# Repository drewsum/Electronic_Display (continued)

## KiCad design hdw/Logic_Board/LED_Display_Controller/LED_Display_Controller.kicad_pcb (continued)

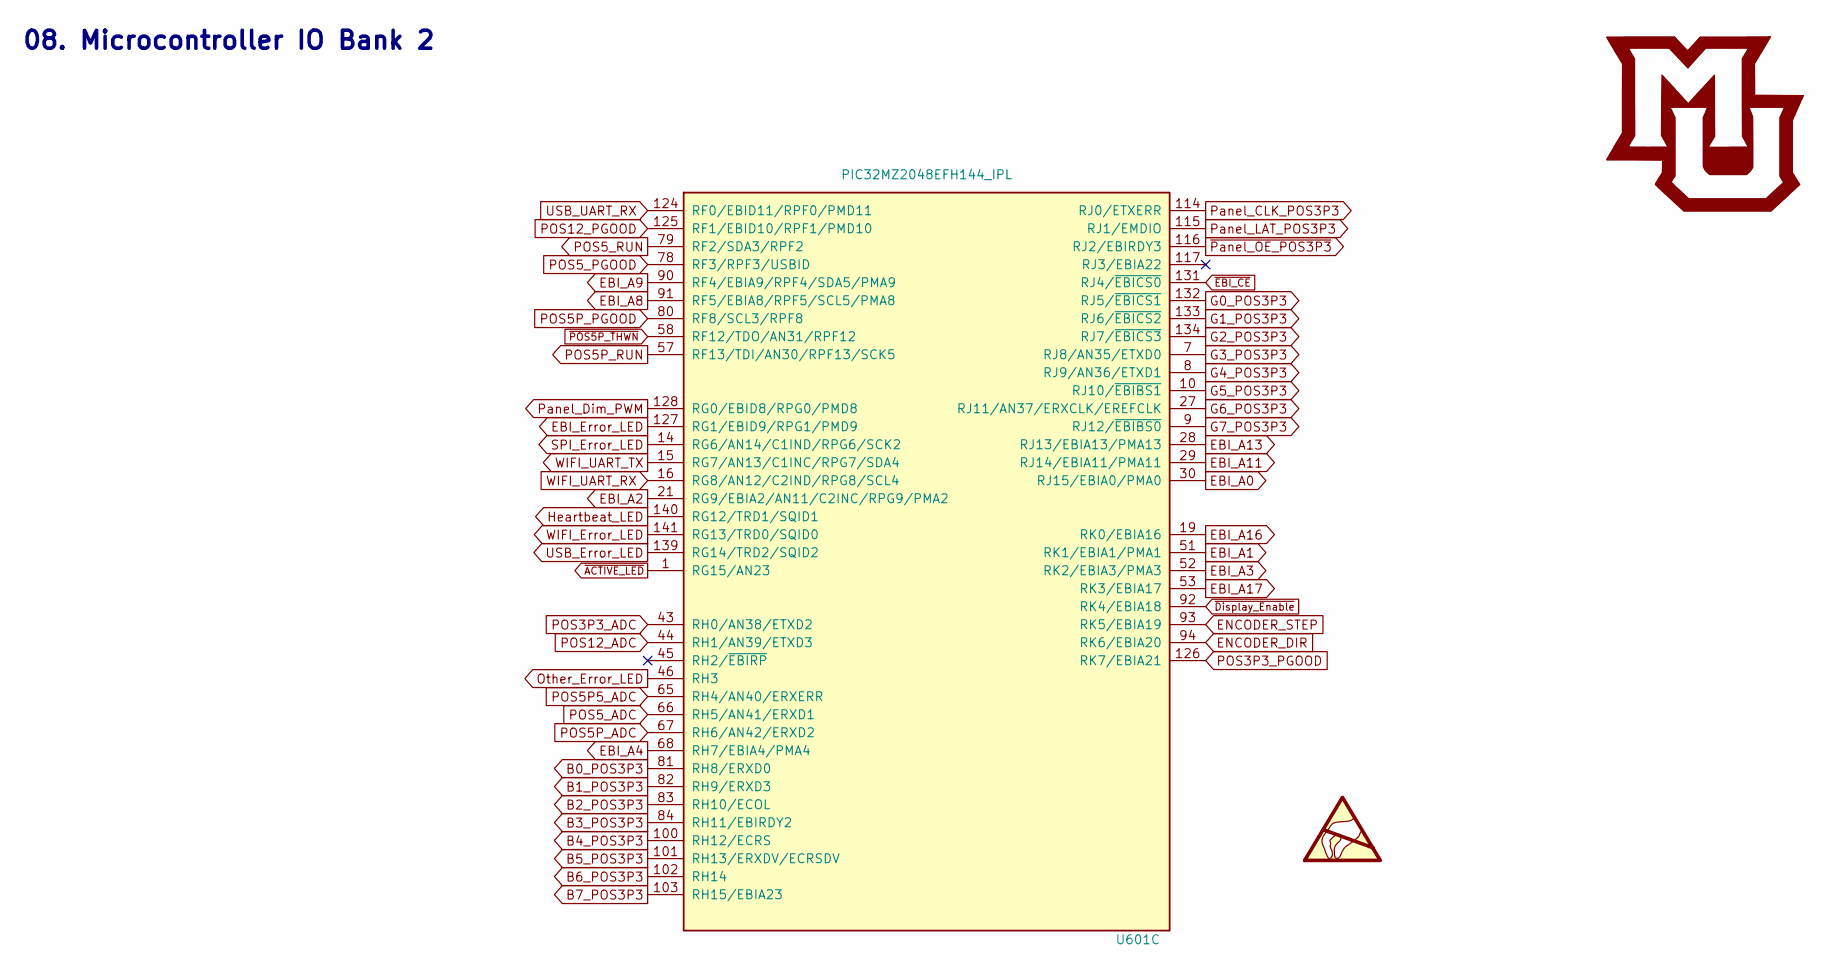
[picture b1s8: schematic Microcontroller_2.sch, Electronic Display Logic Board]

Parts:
U601: PIC32MZ2048EFH144_IPL; TQFP-144_20x20mm_Pitch0.5mm; Digi-Key PN PIC32MZ2048EFH144-I/PL-ND

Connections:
B0_POS3P3: U601.81 (RH8/ERXD0); also elsewhere on the board
B1_POS3P3: U601.82 (RH9/ERXD3); also elsewhere on the board
B2_POS3P3: U601.83 (RH10/ECOL); also elsewhere on the board
B3_POS3P3: U601.84 (RH11/EBIRDY2); also elsewhere on the board
B4_POS3P3: U601.100 (RH12/ECRS); also elsewhere on the board
B5_POS3P3: U601.101 (RH13/ERXDV/ECRSDV); also elsewhere on the board
B6_POS3P3: U601.102 (RH14); also elsewhere on the board
B7_POS3P3: U601.103 (RH15/EBIA23); also elsewhere on the board
EBI_A0: U601.30 (RJ15/EBIA0/PMA0); also elsewhere on the board
EBI_A1: U601.51 (RK1/EBIA1/PMA1); also elsewhere on the board
EBI_A2: U601.21 (RG9/EBIA2/AN11/C2INC/RPG9/PMA2); also elsewhere on the board
EBI_A3: U601.52 (RK2/EBIA3/PMA3); also elsewhere on the board
EBI_A4: U601.68 (RH7/EBIA4/PMA4); also elsewhere on the board
EBI_A8: U601.91 (RF5/EBIA8/RPF5/SCL5/PMA8); also elsewhere on the board
EBI_A9: U601.90 (RF4/EBIA9/RPF4/SDA5/PMA9); also elsewhere on the board
EBI_A11: U601.29 (RJ14/EBIA11/PMA11); also elsewhere on the board
EBI_A13: U601.28 (RJ13/EBIA13/PMA13); also elsewhere on the board
EBI_A16: U601.19 (RK0/EBIA16); also elsewhere on the board
EBI_A17: U601.53 (RK3/EBIA17); also elsewhere on the board
EBI_Error_LED: U601.127 (RG1/EBID9/RPG1/PMD9); also elsewhere on the board
ENCODER_DIR: U601.94 (RK6/EBIA20); also elsewhere on the board
ENCODER_STEP: U601.93 (RK5/EBIA19); also elsewhere on the board
G0_POS3P3: U601.132 (RJ5/~EBICS1~); also elsewhere on the board
G1_POS3P3: U601.133 (RJ6/~EBICS2~); also elsewhere on the board
G2_POS3P3: U601.134 (RJ7/~EBICS3~); also elsewhere on the board
G3_POS3P3: U601.7 (RJ8/AN35/ETXD0); also elsewhere on the board
G4_POS3P3: U601.8 (RJ9/AN36/ETXD1); also elsewhere on the board
G5_POS3P3: U601.10 (RJ10/~EBIBS1~); also elsewhere on the board
G6_POS3P3: U601.27 (RJ11/AN37/ERXCLK/EREFCLK); also elsewhere on the board
G7_POS3P3: U601.9 (RJ12/~EBIBS0~); also elsewhere on the board
Heartbeat_LED: U601.140 (RG12/TRD1/SQID1); also elsewhere on the board
Other_Error_LED: U601.46 (RH3); also elsewhere on the board
POS3P3_ADC: U601.43 (RH0/AN38/ETXD2); also elsewhere on the board
POS3P3_PGOOD: U601.126 (RK7/EBIA21); also elsewhere on the board
POS5P5_ADC: U601.65 (RH4/AN40/ERXERR); also elsewhere on the board
POS5P_ADC: U601.67 (RH6/AN42/ERXD2); also elsewhere on the board
POS5P_PGOOD: U601.80 (RF8/SCL3/RPF8); also elsewhere on the board
POS5P_RUN: U601.57 (RF13/TDI/AN30/RPF13/SCK5); also elsewhere on the board
POS5_ADC: U601.66 (RH5/AN41/ERXD1); also elsewhere on the board
POS5_PGOOD: U601.78 (RF3/RPF3/USBID); also elsewhere on the board
POS5_RUN: U601.79 (RF2/SDA3/RPF2); also elsewhere on the board
POS12_ADC: U601.44 (RH1/AN39/ETXD3); also elsewhere on the board
POS12_PGOOD: U601.125 (RF1/EBID10/RPF1/PMD10); also elsewhere on the board
Panel_CLK_POS3P3: U601.114 (RJ0/ETXERR); also elsewhere on the board
Panel_Dim_PWM: U601.128 (RG0/EBID8/RPG0/PMD8); also elsewhere on the board
Panel_LAT_POS3P3: U601.115 (RJ1/EMDIO); also elsewhere on the board
SPI_Error_LED: U601.14 (RG6/AN14/C1IND/RPG6/SCK2); also elsewhere on the board
USB_Error_LED: U601.139 (RG14/TRD2/SQID2); also elsewhere on the board
USB_UART_RX: U601.124 (RF0/EBID11/RPF0/PMD11); also elsewhere on the board
WIFI_Error_LED: U601.141 (RG13/TRD0/SQID0); also elsewhere on the board
WIFI_UART_RX: U601.16 (RG8/AN12/C2IND/RPG8/SCL4); also elsewhere on the board
WIFI_UART_TX: U601.15 (RG7/AN13/C1INC/RPG7/SDA4); also elsewhere on the board
~ACTIVE_LED: U601.1 (RG15/AN23); also elsewhere on the board
~Display_Enable: U601.92 (RK4/EBIA18); also elsewhere on the board
~EBI_CE: U601.131 (RJ4/~EBICS0~); also elsewhere on the board
~POS5P_THWN: U601.58 (RF12/TDO/AN31/RPF12); also elsewhere on the board
~Panel_OE_POS3P3: U601.116 (RJ2/EBIRDY3); also elsewhere on the board

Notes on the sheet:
08. Microcontroller IO Bank 2

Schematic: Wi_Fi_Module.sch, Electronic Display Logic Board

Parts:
C901: 100uF; CP_Tantalum_Case-B_EIA-3528-21_Reflow; Voltage 6.3V; Tolerance 20%; Digi-Key PN 478-3130-1-ND
C902, C905, C906, C907: 0.1uF; C_0603; Voltage 50V; Digi-Key PN 311-1344-1-ND
C903: 10nF; C_0603; Voltage 50V; Digi-Key PN 1276-1921-1-ND
C904: 1nF; C_0603; Voltage 50V; Digi-Key PN 1276-1018-1-ND
D901: PESD3V3L4UG; SOT-353_SC-70-5; Digi-Key PN 1727-3827-1-ND
D902: Green; LED_0603; Digi-Key PN 160-1446-1-ND
Q901: BSS214NW; SOT-323_SC-70; Digi-Key PN BSS214NWH6327XTSA1CT-ND
R901, R906, R909: 100; R_0603; Tolerance 1%; Digi-Key PN A106047CT-ND
R902, R903, R904, R905, R907, R910, R911: 10k; R_0603; Tolerance 1%; Digi-Key PN RMCF0603FT10K0CT-ND
R908: 10; R_0603; Tolerance 1%; Digi-Key PN YAG3351CT-ND
R912: 0; R_0603; Tolerance 1%; Digi-Key PN 311-0.0GRCT-ND
R913: 1k; R_0603; Tolerance 1%; Digi-Key PN RMCF0603FT1K00CT-ND
U901: ESP8266 Socket; ESP8266_Socket
U902: 74LVC1G00; SOT-353_SC-70-5; Digi-Key PN 296-9846-1-ND
U903: 74LVC1G86; SOT-353_SC-70-5; Digi-Key PN 296-9854-1-ND

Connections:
+3V3: C901.1, C902.1, C903.1, C904.1, C906.1, C907.1, R902.1, R903.1, R905.1, R907.1, R911.1, R913.1, U901.8, U902.5 (VCC), U903.5 (VCC); also elsewhere on the board
GND: C901.2, C902.2, C903.2, C904.2, C905.2, C906.2, C907.2, D901.2 (A), Q901.2 (S), R904.2, R910.2, R912.2, U901.1, U902.3 (GND), U903.3 (GND); also elsewhere on the board
unnamed: C905.1, D901.5 (K4), R905.2, R906.2, U901.6
unnamed: D901.3 (K2), R903.2, R909.2, U901.2
unnamed: D901.4 (K3), R901.2, R902.2, U901.7
unnamed: D902.1 (K), U903.4
unnamed: D902.2 (A), R913.2
unnamed: Q901.1 (G), R907.2, R908.2
unnamed: Q901.3 (D), R906.1
unnamed: R910.1, U902.4, U903.1
unnamed: R911.2, R912.1, U903.2
WIFI_CHPD: D901.1 (K1), R904.1, U901.4; also elsewhere on the board
WIFI_UART_RX: R909.1, U902.1; also elsewhere on the board
WIFI_UART_TX: R901.1, U902.2; also elsewhere on the board
~WIFI_RESET: R908.1; also elsewhere on the board

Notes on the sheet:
09. WiFi Module

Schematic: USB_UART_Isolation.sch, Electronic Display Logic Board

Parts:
C1001, C1003: 0.1uF; C_0603; Voltage 50V; Digi-Key PN 311-1344-1-ND
C1002: 0.56uF; C_2220; Voltage 250VAC; Digi-Key PN 565-4707-1-ND
R1001, R1002, R1007, R1008: 100; R_0603; Tolerance 1%; Digi-Key PN A106047CT-ND
R1003, R1004, R1005, R1006: 10k; R_0603; Tolerance 1%; Digi-Key PN RMCF0603FT10K0CT-ND
U1001: ISO7321C; SOIC-8_3.9x4.9mm_Pitch1.27mm; Digi-Key PN 296-42102-1-ND

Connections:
+3V3: C1001.1, R1003.1, R1004.1, U1001.1 (VCC1); also elsewhere on the board
+5V_USB: C1003.1, R1005.1, R1006.1, U1001.8 (VCC2); also elsewhere on the board
GND: C1001.2, C1002.1, U1001.4 (GND1); also elsewhere on the board
GND_USB: C1002.2, C1003.2, U1001.5 (GND2); also elsewhere on the board
unnamed: R1001.2, R1003.2, U1001.2 (OUTA)
unnamed: R1002.2, R1004.2, U1001.3 (INB)
unnamed: R1005.2, R1008.2, U1001.6 (OUTB)
unnamed: R1006.2, R1007.2, U1001.7 (INA)
USB_UART_RX: R1001.1; also elsewhere on the board
USB_UART_RX_ISO: R1007.1; also elsewhere on the board
USB_UART_TX: R1002.1; also elsewhere on the board
USB_UART_TX_ISO: R1008.1; also elsewhere on the board

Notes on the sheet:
10. USB UART Digital Isolation

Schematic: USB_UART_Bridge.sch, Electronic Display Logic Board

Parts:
C1101, C1102, C1103, C1104, C1105, C1107, C1108, C1111: 0.1uF; C_0603; Voltage 50V; Digi-Key PN 311-1344-1-ND
C1106: 4.7uF; C_0805; Voltage 10V; Digi-Key PN 1276-2972-1-ND
C1109, C1110: 47pF; C_0603; Voltage 50V; Digi-Key PN 478-1171-1-ND
D1101: Green; LED_0603; Digi-Key PN 160-1446-1-ND
D1102: Yellow; LED_0603; Digi-Key PN 160-1448-1-ND
DOC1101: COM_Port_Settings
J1101: USB_B_Mini; USB_Mini-B; Digi-Key PN 732-2109-1-ND
L1101, L1102: 600R 0.5A; L_0603; Digi-Key PN 732-2389-1-ND
R1101, R1105: 10k; R_0603; Tolerance 1%; Digi-Key PN RMCF0603FT10K0CT-ND
R1102: 487k; R_0603; Tolerance 1%; Digi-Key PN 311-487KHRCT-ND
R1103: 6.04k; R_0603; Tolerance 1%; Digi-Key PN RMCF0603FT6K04CT-ND
R1104: 40.2k; R_0603; Tolerance 1%; Digi-Key PN 311-40.2KHRCT-ND
R1106, R1109: 1k; R_0603; Tolerance 1%; Digi-Key PN RMCF0603FT1K00CT-ND
R1107, R1108: 27; R_0603; Tolerance 1%; Digi-Key PN RMCF0603FT27R0CT-ND
U1101: LT6700-1-S6; TSOT-23-6; Digi-Key PN LT6700CS6-1#TRMPBFCT-ND
U1102: FT234XD; DFN-12-1EP_3x3mm_Pitch0.45mm; Digi-Key PN 768-1178-1-ND
U1103: 74LVC1G06; SOT-353_SC-70-5; Digi-Key PN 296-8484-1-ND
U1104: TPD3S014DBVR; SOT-23-6; Digi-Key PN 296-38835-1-ND

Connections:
+5V_USB: C1102.1, C1103.1, C1104.1, C1105.1, C1106.1, C1108.1, R1101.1, R1102.1, R1105.1, R1106.1, R1109.1, U1101.5 (Vs), U1102.4 (VCC), U1102.9 (VCCIO), U1103.5 (VCC), U1104.4 (OUT); also elsewhere on the board
/USB UART Bridge/BRIDGE_USB+: R1107.2, U1102.12 (USBDP)
/USB UART Bridge/BRIDGE_USB-: R1108.2, U1102.1 (USBDM)
/USB UART Bridge/CONN_USB+: C1109.1, J1101.3 (D+), R1107.1, U1104.6 (D1)
/USB UART Bridge/CONN_USB-: C1110.1, J1101.2 (D-), R1108.1, U1104.5 (D2)
/USB UART Bridge/POS5_USB_PGOOD: R1105.2, U1101.1 (OUTA), U1101.6 (OUTB), U1103.2
GND_USB: C1101.2, C1102.2, C1103.2, C1104.2, C1105.2, C1106.2, C1107.2, C1108.2, C1109.2, C1110.2, C1111.2, J1101.5 (GND), L1102.1, R1104.2, U1101.2 (GND), U1102.5 (GND), U1102.13 (GND), U1103.3 (GND), U1104.2 (GND); also elsewhere on the board
unnamed: C1101.1, R1101.2, U1102.2 (~RESET)
unnamed: C1107.1, U1102.3 (3V3OUT)
unnamed: C1111.1, L1101.2, U1104.1 (EN), U1104.3 (IN)
unnamed: D1101.1 (K), U1103.4
unnamed: D1101.2 (A), R1106.2
unnamed: D1102.2 (A), R1109.2
unnamed: J1101.1 (VBUS), L1101.1
unnamed: J1101.6 (Shield), L1102.2
unnamed: R1102.2, R1103.1, U1101.3 (+INA)
unnamed: R1103.2, R1104.1, U1101.4 (-INB)
USB_UART_RX_ISO: U1102.7 (TXD); also elsewhere on the board
USB_UART_TX_ISO: U1102.10 (RXD); also elsewhere on the board
~USB_ACTIVE: D1102.1 (K), U1102.6 (CBUS0)

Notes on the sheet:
11. USB UART Bridge

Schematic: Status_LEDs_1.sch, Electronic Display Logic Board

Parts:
C1201, C1202, C1203, C1204, C1205, C1206, C1207, C1208, C1209, C1210, C1211, C1212, C1213, C1214: 0.1uF; C_0603; Voltage 50V; Digi-Key PN 311-1344-1-ND
D1201, D1202, D1203, D1204, D1205, D1207: Red; LED_0603; Digi-Key PN 160-1447-1-ND
D1206, D1208, D1209, D1210, D1211, D1212, D1213: Green; LED_0603; Digi-Key PN 160-1446-1-ND
R1201, R1202, R1205, R1206, R1209, R1210, R1213, R1215, R1217, R1219, R1221, R1222, R1227, R1228, R1231: 10k; R_0603; Tolerance 1%; Digi-Key PN RMCF0603FT10K0CT-ND
R1203, R1204, R1207, R1208, R1211, R1212, R1214, R1216, R1218, R1220, R1223, R1229, R1230: 1k; R_0603; Tolerance 1%; Digi-Key PN RMCF0603FT1K00CT-ND
R1224, R1225, R1226: 0; R_0603; Tolerance 1%; Digi-Key PN 311-0.0GRCT-ND
U1201, U1202, U1203, U1204, U1205, U1206, U1207, U1208, U1209, U1210, U1211, U1213, U1214: 74LVC1G06; SOT-353_SC-70-5; Digi-Key PN 296-8484-1-ND
U1212: 4040; TSSOP-16_4.4x5mm_Pitch0.65mm; Digi-Key PN 296-12761-1-ND

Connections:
+3V3: C1201.1, C1202.1, C1203.1, C1204.1, C1205.1, C1206.1, C1207.1, C1208.1, C1209.1, C1210.1, C1211.1, C1212.1, C1213.1, C1214.1, R1201.1, R1203.1, R1204.1, R1207.1, R1208.1, R1211.1, R1212.1, R1214.1, R1216.1, R1218.1, R1220.1, R1223.1, R1229.1, R1230.1, R1231.1, U1201.5 (VCC), U1202.5 (VCC), U1203.5 (VCC), U1204.5 (VCC), U1205.5 (VCC), U1206.5 (VCC), U1207.5 (VCC), U1208.5 (VCC), U1209.5 (VCC), U1210.5 (VCC), U1211.5 (VCC), U1212.16 (VDD), U1213.5 (VCC), U1214.5 (VCC); also elsewhere on the board
EBI_Error_LED: R1206.1, U1204.2; also elsewhere on the board
GND: C1201.2, C1202.2, C1203.2, C1204.2, C1205.2, C1206.2, C1207.2, C1208.2, C1209.2, C1210.2, C1211.2, C1212.2, C1213.2, C1214.2, R1202.2, R1205.2, R1206.2, R1209.2, R1210.2, R1213.2, R1215.2, R1217.2, R1219.2, R1221.2, R1222.2, R1227.2, R1228.2, U1201.3 (GND), U1202.3 (GND), U1203.3 (GND), U1204.3 (GND), U1205.3 (GND), U1206.3 (GND), U1207.3 (GND), U1208.3 (GND), U1209.3 (GND), U1210.3 (GND), U1211.3 (GND), U1212.8 (VSS), U1213.3 (GND), U1214.3 (GND); also elsewhere on the board
Heartbeat_LED: R1210.1, U1206.2; also elsewhere on the board
unnamed: D1201.1 (K), U1201.4
unnamed: D1201.2 (A), R1203.2
unnamed: D1202.1 (K), U1202.4
unnamed: D1202.2 (A), R1204.2
unnamed: D1203.1 (K), U1203.4
unnamed: D1203.2 (A), R1207.2
unnamed: D1204.1 (K), U1204.4
unnamed: D1204.2 (A), R1208.2
unnamed: D1205.1 (K), U1205.4
unnamed: D1205.2 (A), R1211.2
unnamed: D1206.1 (K), U1206.4
unnamed: D1206.2 (A), R1212.2
unnamed: D1207.1 (K), U1207.4
unnamed: D1207.2 (A), R1214.2
unnamed: D1208.1 (K), U1208.4
unnamed: D1208.2 (A), R1216.2
unnamed: D1209.1 (K), U1209.4
unnamed: D1209.2 (A), R1218.2
unnamed: D1210.1 (K), U1210.4
unnamed: D1210.2 (A), R1220.2
unnamed: D1211.1 (K), U1211.4
unnamed: D1211.2 (A), R1223.2
unnamed: D1212.1 (K), U1213.4
unnamed: D1212.2 (A), R1229.2
unnamed: D1213.1 (K), U1214.4
unnamed: D1213.2 (A), R1230.2
unnamed: R1221.1, U1212.11 (Reset)
unnamed: R1224.1, R1225.1, R1226.1, R1228.1, U1214.2
unnamed: R1224.2, U1212.3 (Q4)
unnamed: R1225.2, U1212.4 (Q6)
unnamed: R1226.2, U1212.15 (Q10)
Other_Error_LED: R1213.1, U1207.2; also elsewhere on the board
Panel_LAT_POS3P3: R1231.2, U1212.10 (CLK); also elsewhere on the board
Row_A_POS3P3: R1222.1, U1211.2; also elsewhere on the board
Row_B_POS3P3: R1227.1, U1213.2; also elsewhere on the board
Row_C_POS3P3: R1215.1, U1208.2; also elsewhere on the board
Row_D_POS3P3: R1217.1, U1209.2; also elsewhere on the board
Row_E_POS3P3: R1219.1, U1210.2; also elsewhere on the board
SPI_Error_LED: R1202.1, U1202.2; also elsewhere on the board
USB_Error_LED: R1209.1, U1205.2; also elsewhere on the board
WIFI_Error_LED: R1205.1, U1203.2; also elsewhere on the board
~ACTIVE_LED: R1201.2, U1201.2; also elsewhere on the board

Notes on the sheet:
12. Status LEDs Bank 1

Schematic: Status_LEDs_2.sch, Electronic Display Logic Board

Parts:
C1301, C1302, C1303, C1304: 0.1uF; C_0603; Voltage 50V; Digi-Key PN 311-1344-1-ND
D1301, D1302, D1303, D1304: Green; LED_0603; Digi-Key PN 160-1446-1-ND
R1301, R1302, R1303, R1304: 1k; R_0603; Tolerance 1%; Digi-Key PN RMCF0603FT1K00CT-ND
U1301, U1302, U1303, U1304: 74LVC1G06; SOT-353_SC-70-5; Digi-Key PN 296-8484-1-ND

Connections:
+3V3: C1301.1, C1302.1, C1303.1, C1304.1, R1301.1, R1302.1, R1303.1, R1304.1, U1301.5 (VCC), U1302.5 (VCC), U1303.5 (VCC), U1304.5 (VCC); also elsewhere on the board
GND: C1301.2, C1302.2, C1303.2, C1304.2, U1301.3 (GND), U1302.3 (GND), U1303.3 (GND), U1304.3 (GND); also elsewhere on the board
unnamed: D1301.1 (K), U1301.4
unnamed: D1301.2 (A), R1301.2
unnamed: D1302.1 (K), U1302.4
unnamed: D1302.2 (A), R1302.2
unnamed: D1303.1 (K), U1303.4
unnamed: D1303.2 (A), R1303.2
unnamed: D1304.1 (K), U1304.4
unnamed: D1304.2 (A), R1304.2
POS3P3_PGOOD: U1302.2; also elsewhere on the board
POS5P_PGOOD: U1304.2; also elsewhere on the board
POS5_PGOOD: U1303.2; also elsewhere on the board
POS12_PGOOD: U1301.2; also elsewhere on the board

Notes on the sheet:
13. Status LEDs Bank 2

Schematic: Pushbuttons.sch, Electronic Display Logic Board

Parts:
C1401, C1402, C1403, C1404, C1405: 0.1uF; C_0603; Voltage 50V; Digi-Key PN 311-1344-1-ND
D1401: PESD3V3L4UG; SOT-353_SC-70-5; Digi-Key PN 1727-3827-1-ND
J1401: Encoder Ext; Pin_Header_Straight_1x05_Pitch2.54mm
R1401, R1402, R1405, R1406, R1407, R1408: 10k; R_0603; Tolerance 1%; Digi-Key PN RMCF0603FT10K0CT-ND
R1403, R1404: 1k; R_0603; Tolerance 1%; Digi-Key PN RMCF0603FT1K00CT-ND
SW1401: Display Enable; SW_PUSH_6mm
SW1402: Brightness/Enable; ACZ11BR4E-15FA1-20C; Digi-Key PN 102-1753-ND
U1401: MAX6816; SOT-143; Digi-Key PN MAX6816EUS+TCT-ND
U1402: 74LVC2G14; SOT-363_SC-70-6; Digi-Key PN 296-13011-1-ND
U1403: 74LVC1G79; SOT-353_SC-70-5; Digi-Key PN 296-9850-1-ND

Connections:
+3V3: C1401.1, C1404.1, C1405.1, R1401.1, R1402.1, R1405.1, U1401.4 (Vcc), U1402.5 (VCC), U1403.5 (VCC); also elsewhere on the board
ENCODER_DIR: R1408.1, U1403.4 (Q); also elsewhere on the board
ENCODER_STEP: R1407.1, U1402.6, U1403.1 (D); also elsewhere on the board
GND: C1401.2, C1402.2, C1403.2, C1404.2, C1405.2, D1401.2 (A), J1401.2, J1401.5, R1406.2, R1407.2, R1408.2, SW1401.1, SW1402.C, SW1402.S2, U1401.1 (GND), U1402.2 (GND), U1403.3 (GND); also elsewhere on the board
unnamed: C1402.1, R1404.1, U1402.3
unnamed: C1403.1, R1403.1, U1402.1
unnamed: D1401.1 (K1), J1401.1, R1402.2, R1404.2, SW1402.B
unnamed: D1401.3 (K2), J1401.3, R1401.2, R1403.2, SW1402.A
unnamed: D1401.4 (K3), J1401.4, SW1401.2, SW1402.S1, U1401.2 (In)
unnamed: R1406.1, U1402.4, U1403.2 (C)
~Display_Enable: R1405.2, U1401.3 (Out); also elsewhere on the board

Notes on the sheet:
Turning rotary encoder will adjust display master brightness Pressing encoder switch will toggle display on/off state
14. Pushbuttons

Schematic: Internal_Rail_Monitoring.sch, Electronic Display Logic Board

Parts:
C1501, C1502, C1503, C1504, C1505: 330pF; C_0603; Voltage 50V; Digi-Key PN 399-6880-1-ND
D1501, D1502, D1503, D1504, D1505: BZT52C3V3T; D_SOD-523; Digi-Key PN BZT52C3V3T-TPMSCT-ND
R1501, R1502, R1503, R1504, R1505, R1506, R1507, R1508, R1509: 10k; R_0603; Tolerance 1%; Digi-Key PN RMCF0603FT10K0CT-ND
R1510: 1k; R_0603; Tolerance 1%; Digi-Key PN RMCF0603FT1K00CT-ND

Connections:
+3V3: R1501.1; also elsewhere on the board
+5.5V: R1507.1; also elsewhere on the board
+5V: R1505.1; also elsewhere on the board
+5VP: R1503.1; also elsewhere on the board
+12V: R1509.1; also elsewhere on the board
GND: C1501.2, C1502.2, C1503.2, C1504.2, C1505.2, D1501.2 (A), D1502.2 (A), D1503.2 (A), D1504.2 (A), D1505.2 (A), R1502.2, R1504.2, R1506.2, R1508.2, R1510.2; also elsewhere on the board
POS3P3_ADC: C1501.1, D1501.1 (K), R1501.2, R1502.1; also elsewhere on the board
POS5P5_ADC: C1504.1, D1504.1 (K), R1507.2, R1508.1; also elsewhere on the board
POS5P_ADC: C1502.1, D1502.1 (K), R1503.2, R1504.1; also elsewhere on the board
POS5_ADC: C1503.1, D1503.1 (K), R1505.2, R1506.1; also elsewhere on the board
POS12_ADC: C1505.1, D1505.1 (K), R1509.2, R1510.1; also elsewhere on the board

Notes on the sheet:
15. Internal Rail Monitoring

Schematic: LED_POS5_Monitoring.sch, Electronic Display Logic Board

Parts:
C1601: 10uF; CP_Tantalum_Case-B_EIA-3528-21_Reflow; Voltage 16V; Tolerance 10%; Digi-Key PN 478-8236-1-ND
C1602, C1603, C1604, C1605, C1607, C1608, C1609: 0.1uF; C_0603; Voltage 50V; Digi-Key PN 311-1344-1-ND
C1606: 100uF; CP_Tantalum_Case-B_EIA-3528-21_Reflow; Voltage 6.3V; Tolerance 20%; Digi-Key PN 478-3130-1-ND
J1601: POS5P EXT; Pin_Header_Straight_1x02_Pitch2.54mm
J1602: POS5P PGOOD; Pin_Header_Straight_1x02_Pitch2.54mm
J1603: POS5P_THWN; Pin_Header_Straight_1x02_Pitch2.54mm
J1604: POS5P_RUN; Pin_Header_Straight_1x02_Pitch2.54mm
R1601: 200; R_0603; Tolerance 1%; Digi-Key PN P200HCT-ND
R1602: 680; R_0603; Tolerance 1%; Digi-Key PN P680HCT-ND
R1603, R1604: 1k; R_0603; Tolerance 1%; Digi-Key PN RMCF0603FT1K00CT-ND
R1605, R1606, R1607, R1608, R1609, R1610: 10k; R_0603; Tolerance 1%; Digi-Key PN RMCF0603FT10K0CT-ND
U1601: LM1117-ADJ; SOT-223-3_TabPin2; Digi-Key PN LM1117IMPX-ADJ/NOPBCT-ND
U1602, U1606: NUP2202; SOT-363_SC-70-6; Digi-Key PN NUP2202W1T2GOSCT-ND
U1603, U1604, U1605: 74LVC1G17; SOT-353_SC-70-5; Digi-Key PN 296-11934-1-ND

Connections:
+3V3: C1608.1, C1609.1, U1604.5 (VCC), U1605.5 (VCC); also elsewhere on the board
+5.5V: C1605.1, C1606.1, C1607.1, R1601.1, U1601.2 (VO), U1602.5, U1603.5 (VCC), U1606.5; also elsewhere on the board
+5VP: C1604.1, J1601.1; also elsewhere on the board
+12V: C1601.1, C1602.1, U1601.3 (VI); also elsewhere on the board
GND: C1601.2, C1602.2, C1603.2, C1604.2, C1605.2, C1606.2, C1607.2, C1608.2, C1609.2, J1601.2, J1602.2, J1603.2, J1604.2, R1602.2, R1605.2, R1606.2, R1607.2, R1608.2, R1609.2, R1610.2, U1602.2, U1603.3 (GND), U1604.3 (GND), U1605.3 (GND), U1606.2; also elsewhere on the board
unnamed: C1603.1, R1601.2, R1602.1, U1601.1 (ADJ)
unnamed: J1602.1, R1603.2
unnamed: J1603.1, R1604.2
unnamed: J1604.1, R1608.1, U1603.4, U1606.1
unnamed: R1603.1, R1606.1, U1602.6, U1604.2
unnamed: R1604.1, R1607.1, U1602.1, U1605.2
POS5P_PGOOD: R1609.1, U1604.4; also elsewhere on the board
POS5P_RUN: R1605.1, U1603.2; also elsewhere on the board
~POS5P_THWN: R1610.1, U1605.4; also elsewhere on the board

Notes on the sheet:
All headers on this sheet interface with power board to power panels
16. LED Power Supply Monitoring

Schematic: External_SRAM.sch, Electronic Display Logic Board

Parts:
C1701, C1704: 0.1uF; C_0603; Voltage 50V; Digi-Key PN 311-1344-1-ND
C1702, C1705: 10nF; C_0603; Voltage 50V; Digi-Key PN 1276-1921-1-ND
C1703, C1706: 1nF; C_0603; Voltage 50V; Digi-Key PN 1276-1018-1-ND
U1701: CY7C1010DV33; TSSOP-44_11x18.25mm_Pitch0.8mm; Digi-Key PN 428-1960-ND

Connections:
+3V3: C1701.1, C1702.1, C1703.1, C1704.1, C1705.1, C1706.1, U1701.11 (VCC), U1701.33 (VCC); also elsewhere on the board
EBI_A0: U1701.7 (A0); also elsewhere on the board
EBI_A1: U1701.6 (A1); also elsewhere on the board
EBI_A2: U1701.5 (A2); also elsewhere on the board
EBI_A3: U1701.4 (A3); also elsewhere on the board
EBI_A4: U1701.3 (A4); also elsewhere on the board
EBI_A5: U1701.41 (A5); also elsewhere on the board
EBI_A6: U1701.40 (A6); also elsewhere on the board
EBI_A7: U1701.39 (A7); also elsewhere on the board
EBI_A8: U1701.38 (A8); also elsewhere on the board
EBI_A9: U1701.30 (A9); also elsewhere on the board
EBI_A10: U1701.29 (A10); also elsewhere on the board
EBI_A11: U1701.28 (A11); also elsewhere on the board
EBI_A12: U1701.27 (A12); also elsewhere on the board
EBI_A13: U1701.20 (A13); also elsewhere on the board
EBI_A14: U1701.19 (A14); also elsewhere on the board
EBI_A15: U1701.18 (A15); also elsewhere on the board
EBI_A16: U1701.17 (A16); also elsewhere on the board
EBI_A17: U1701.16 (A17); also elsewhere on the board
EBI_IO0: U1701.9 (IO0); also elsewhere on the board
EBI_IO1: U1701.10 (IO1); also elsewhere on the board
EBI_IO2: U1701.13 (IO2); also elsewhere on the board
EBI_IO3: U1701.14 (IO3); also elsewhere on the board
EBI_IO4: U1701.31 (IO4); also elsewhere on the board
EBI_IO5: U1701.32 (IO5); also elsewhere on the board
EBI_IO6: U1701.35 (IO6); also elsewhere on the board
EBI_IO7: U1701.36 (IO7); also elsewhere on the board
GND: C1701.2, C1702.2, C1703.2, C1704.2, C1705.2, C1706.2, U1701.12 (VSS), U1701.34 (VSS); also elsewhere on the board
~EBI_CE: U1701.8 (~CE); also elsewhere on the board
~EBI_OE: U1701.37 (~OE); also elsewhere on the board
~EBI_WE: U1701.15 (~WE); also elsewhere on the board

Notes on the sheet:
External SRAM stores the current slide being displayed Each of the eight programmed slides are stored in external serial flash
17. External SRAM

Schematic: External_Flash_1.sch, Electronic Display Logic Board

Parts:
C1801, C1804: 0.1uF; C_0603; Voltage 50V; Digi-Key PN 311-1344-1-ND
C1802: 10nF; C_0603; Voltage 50V; Digi-Key PN 1276-1921-1-ND
C1803: 1nF; C_0603; Voltage 50V; Digi-Key PN 1276-1018-1-ND
D1801: Green; LED_0603; Digi-Key PN 160-1446-1-ND
R1801, R1802, R1803, R1804, R1805, R1812: 100; R_0603; Tolerance 1%; Digi-Key PN A106047CT-ND
R1806, R1807, R1808, R1809, R1810, R1811: 10k; R_0603; Tolerance 1%; Digi-Key PN RMCF0603FT10K0CT-ND
R1813: 1k; R_0603; Tolerance 1%; Digi-Key PN RMCF0603FT1K00CT-ND
U1801: SST25PF020B; SOIC-8_3.9x4.9mm_Pitch1.27mm; Digi-Key PN SST25PF020B-80-4C-SAE-TCT-ND
U1802: 74LVC1G07; SOT-353_SC-70-5; Digi-Key PN 296-8486-1-ND

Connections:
+3V3: C1801.1, C1802.1, C1803.1, C1804.1, R1806.1, R1807.1, R1809.1, R1813.1, U1801.8 (VDD), U1802.5 (VCC); also elsewhere on the board
FLASH_MISO: R1812.1; also elsewhere on the board
FLASH_MOSI: R1801.2; also elsewhere on the board
FLASH_SCK: R1805.2; also elsewhere on the board
GND: C1801.2, C1802.2, C1803.2, C1804.2, R1808.2, R1810.2, R1811.2, U1801.4 (VSS), U1802.3 (GND); also elsewhere on the board
unnamed: D1801.1 (K), U1802.4
unnamed: D1801.2 (A), R1813.2
unnamed: R1801.1, R1810.1, U1801.5 (SI)
unnamed: R1802.1, R1809.2, U1801.7 (~HOLD)
unnamed: R1803.1, R1806.2, U1801.3 (~WP)
unnamed: R1804.1, R1807.2, U1801.1 (~CE)
unnamed: R1805.1, R1808.1, U1801.6 (SCK)
unnamed: R1811.1, R1812.2, U1801.2 (SO)
~FLASH_CE1: R1804.2, U1802.2; also elsewhere on the board
~FLASH_Hold: R1802.2; also elsewhere on the board
~FLASH_WP1: R1803.2; also elsewhere on the board

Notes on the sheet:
18. External FLASH 1

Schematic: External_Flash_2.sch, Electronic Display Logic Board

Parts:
C1901, C1904: 0.1uF; C_0603; Voltage 50V; Digi-Key PN 311-1344-1-ND
C1902: 10nF; C_0603; Voltage 50V; Digi-Key PN 1276-1921-1-ND
C1903: 1nF; C_0603; Voltage 50V; Digi-Key PN 1276-1018-1-ND
D1901: Green; LED_0603; Digi-Key PN 160-1446-1-ND
R1901, R1902, R1903, R1904, R1905, R1912: 100; R_0603; Tolerance 1%; Digi-Key PN A106047CT-ND
R1906, R1907, R1908, R1909, R1910, R1911: 10k; R_0603; Tolerance 1%; Digi-Key PN RMCF0603FT10K0CT-ND
R1913: 1k; R_0603; Tolerance 1%; Digi-Key PN RMCF0603FT1K00CT-ND
U1901: SST25PF020B; SOIC-8_3.9x4.9mm_Pitch1.27mm; Digi-Key PN SST25PF020B-80-4C-SAE-TCT-ND
U1902: 74LVC1G07; SOT-353_SC-70-5; Digi-Key PN 296-8486-1-ND

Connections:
+3V3: C1901.1, C1902.1, C1903.1, C1904.1, R1906.1, R1907.1, R1909.1, R1913.1, U1901.8 (VDD), U1902.5 (VCC); also elsewhere on the board
FLASH_MISO: R1912.1; also elsewhere on the board
FLASH_MOSI: R1901.2; also elsewhere on the board
FLASH_SCK: R1905.2; also elsewhere on the board
GND: C1901.2, C1902.2, C1903.2, C1904.2, R1908.2, R1910.2, R1911.2, U1901.4 (VSS), U1902.3 (GND); also elsewhere on the board
unnamed: D1901.1 (K), U1902.4
unnamed: D1901.2 (A), R1913.2
unnamed: R1901.1, R1910.1, U1901.5 (SI)
unnamed: R1902.1, R1909.2, U1901.7 (~HOLD)
unnamed: R1903.1, R1906.2, U1901.3 (~WP)
unnamed: R1904.1, R1907.2, U1901.1 (~CE)
unnamed: R1905.1, R1908.1, U1901.6 (SCK)
unnamed: R1911.1, R1912.2, U1901.2 (SO)
~FLASH_CE2: R1904.2, U1902.2; also elsewhere on the board
~FLASH_Hold: R1902.2; also elsewhere on the board
~FLASH_WP2: R1903.2; also elsewhere on the board

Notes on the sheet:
19. External FLASH 2

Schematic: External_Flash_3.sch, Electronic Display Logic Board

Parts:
C2001, C2004: 0.1uF; C_0603; Voltage 50V; Digi-Key PN 311-1344-1-ND
C2002: 10nF; C_0603; Voltage 50V; Digi-Key PN 1276-1921-1-ND
C2003: 1nF; C_0603; Voltage 50V; Digi-Key PN 1276-1018-1-ND
D2001: Green; LED_0603; Digi-Key PN 160-1446-1-ND
R2001, R2002, R2003, R2004, R2005, R2012: 100; R_0603; Tolerance 1%; Digi-Key PN A106047CT-ND
R2006, R2007, R2008, R2009, R2010, R2011: 10k; R_0603; Tolerance 1%; Digi-Key PN RMCF0603FT10K0CT-ND
R2013: 1k; R_0603; Tolerance 1%; Digi-Key PN RMCF0603FT1K00CT-ND
U2001: SST25PF020B; SOIC-8_3.9x4.9mm_Pitch1.27mm; Digi-Key PN SST25PF020B-80-4C-SAE-TCT-ND
U2002: 74LVC1G07; SOT-353_SC-70-5; Digi-Key PN 296-8486-1-ND

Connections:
+3V3: C2001.1, C2002.1, C2003.1, C2004.1, R2006.1, R2007.1, R2009.1, R2013.1, U2001.8 (VDD), U2002.5 (VCC); also elsewhere on the board
FLASH_MISO: R2012.1; also elsewhere on the board
FLASH_MOSI: R2001.2; also elsewhere on the board
FLASH_SCK: R2005.2; also elsewhere on the board
GND: C2001.2, C2002.2, C2003.2, C2004.2, R2008.2, R2010.2, R2011.2, U2001.4 (VSS), U2002.3 (GND); also elsewhere on the board
unnamed: D2001.1 (K), U2002.4
unnamed: D2001.2 (A), R2013.2
unnamed: R2001.1, R2010.1, U2001.5 (SI)
unnamed: R2002.1, R2009.2, U2001.7 (~HOLD)
unnamed: R2003.1, R2006.2, U2001.3 (~WP)
unnamed: R2004.1, R2007.2, U2001.1 (~CE)
unnamed: R2005.1, R2008.1, U2001.6 (SCK)
unnamed: R2011.1, R2012.2, U2001.2 (SO)
~FLASH_CE3: R2004.2, U2002.2; also elsewhere on the board
~FLASH_Hold: R2002.2; also elsewhere on the board
~FLASH_WP3: R2003.2; also elsewhere on the board

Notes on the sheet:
20. External FLASH 3

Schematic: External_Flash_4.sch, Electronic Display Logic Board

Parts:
C2101, C2104: 0.1uF; C_0603; Voltage 50V; Digi-Key PN 311-1344-1-ND
C2102: 10nF; C_0603; Voltage 50V; Digi-Key PN 1276-1921-1-ND
C2103: 1nF; C_0603; Voltage 50V; Digi-Key PN 1276-1018-1-ND
D2101: Green; LED_0603; Digi-Key PN 160-1446-1-ND
R2101, R2102, R2103, R2104, R2105, R2112: 100; R_0603; Tolerance 1%; Digi-Key PN A106047CT-ND
R2106, R2107, R2108, R2109, R2110, R2111: 10k; R_0603; Tolerance 1%; Digi-Key PN RMCF0603FT10K0CT-ND
R2113: 1k; R_0603; Tolerance 1%; Digi-Key PN RMCF0603FT1K00CT-ND
U2101: SST25PF020B; SOIC-8_3.9x4.9mm_Pitch1.27mm; Digi-Key PN SST25PF020B-80-4C-SAE-TCT-ND
U2102: 74LVC1G07; SOT-353_SC-70-5; Digi-Key PN 296-8486-1-ND

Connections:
+3V3: C2101.1, C2102.1, C2103.1, C2104.1, R2106.1, R2107.1, R2109.1, R2113.1, U2101.8 (VDD), U2102.5 (VCC); also elsewhere on the board
FLASH_MISO: R2112.1; also elsewhere on the board
FLASH_MOSI: R2101.2; also elsewhere on the board
FLASH_SCK: R2105.2; also elsewhere on the board
GND: C2101.2, C2102.2, C2103.2, C2104.2, R2108.2, R2110.2, R2111.2, U2101.4 (VSS), U2102.3 (GND); also elsewhere on the board
unnamed: D2101.1 (K), U2102.4
unnamed: D2101.2 (A), R2113.2
unnamed: R2101.1, R2110.1, U2101.5 (SI)
unnamed: R2102.1, R2109.2, U2101.7 (~HOLD)
unnamed: R2103.1, R2106.2, U2101.3 (~WP)
unnamed: R2104.1, R2107.2, U2101.1 (~CE)
unnamed: R2105.1, R2108.1, U2101.6 (SCK)
unnamed: R2111.1, R2112.2, U2101.2 (SO)
~FLASH_CE4: R2104.2, U2102.2; also elsewhere on the board
~FLASH_Hold: R2102.2; also elsewhere on the board
~FLASH_WP4: R2103.2; also elsewhere on the board

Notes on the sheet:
21. External FLASH 4

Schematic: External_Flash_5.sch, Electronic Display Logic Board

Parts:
C2201, C2204: 0.1uF; C_0603; Voltage 50V; Digi-Key PN 311-1344-1-ND
C2202: 10nF; C_0603; Voltage 50V; Digi-Key PN 1276-1921-1-ND
C2203: 1nF; C_0603; Voltage 50V; Digi-Key PN 1276-1018-1-ND
D2201: Green; LED_0603; Digi-Key PN 160-1446-1-ND
R2201, R2202, R2203, R2204, R2205, R2212: 100; R_0603; Tolerance 1%; Digi-Key PN A106047CT-ND
R2206, R2207, R2208, R2209, R2210, R2211: 10k; R_0603; Tolerance 1%; Digi-Key PN RMCF0603FT10K0CT-ND
R2213: 1k; R_0603; Tolerance 1%; Digi-Key PN RMCF0603FT1K00CT-ND
U2201: SST25PF020B; SOIC-8_3.9x4.9mm_Pitch1.27mm; Digi-Key PN SST25PF020B-80-4C-SAE-TCT-ND
U2202: 74LVC1G07; SOT-353_SC-70-5; Digi-Key PN 296-8486-1-ND

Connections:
+3V3: C2201.1, C2202.1, C2203.1, C2204.1, R2206.1, R2207.1, R2209.1, R2213.1, U2201.8 (VDD), U2202.5 (VCC); also elsewhere on the board
FLASH_MISO: R2212.1; also elsewhere on the board
FLASH_MOSI: R2201.2; also elsewhere on the board
FLASH_SCK: R2205.2; also elsewhere on the board
GND: C2201.2, C2202.2, C2203.2, C2204.2, R2208.2, R2210.2, R2211.2, U2201.4 (VSS), U2202.3 (GND); also elsewhere on the board
unnamed: D2201.1 (K), U2202.4
unnamed: D2201.2 (A), R2213.2
unnamed: R2201.1, R2210.1, U2201.5 (SI)
unnamed: R2202.1, R2209.2, U2201.7 (~HOLD)
unnamed: R2203.1, R2206.2, U2201.3 (~WP)
unnamed: R2204.1, R2207.2, U2201.1 (~CE)
unnamed: R2205.1, R2208.1, U2201.6 (SCK)
unnamed: R2211.1, R2212.2, U2201.2 (SO)
~FLASH_CE5: R2204.2, U2202.2; also elsewhere on the board
~FLASH_Hold: R2202.2; also elsewhere on the board
~FLASH_WP5: R2203.2; also elsewhere on the board

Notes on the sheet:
22. External FLASH 5

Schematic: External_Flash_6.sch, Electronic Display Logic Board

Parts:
C2301, C2304: 0.1uF; C_0603; Voltage 50V; Digi-Key PN 311-1344-1-ND
C2302: 10nF; C_0603; Voltage 50V; Digi-Key PN 1276-1921-1-ND
C2303: 1nF; C_0603; Voltage 50V; Digi-Key PN 1276-1018-1-ND
D2301: Green; LED_0603; Digi-Key PN 160-1446-1-ND
R2301, R2302, R2303, R2304, R2305, R2312: 100; R_0603; Tolerance 1%; Digi-Key PN A106047CT-ND
R2306, R2307, R2308, R2309, R2310, R2311: 10k; R_0603; Tolerance 1%; Digi-Key PN RMCF0603FT10K0CT-ND
R2313: 1k; R_0603; Tolerance 1%; Digi-Key PN RMCF0603FT1K00CT-ND
U2301: SST25PF020B; SOIC-8_3.9x4.9mm_Pitch1.27mm; Digi-Key PN SST25PF020B-80-4C-SAE-TCT-ND
U2302: 74LVC1G07; SOT-353_SC-70-5; Digi-Key PN 296-8486-1-ND

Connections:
+3V3: C2301.1, C2302.1, C2303.1, C2304.1, R2306.1, R2307.1, R2309.1, R2313.1, U2301.8 (VDD), U2302.5 (VCC); also elsewhere on the board
FLASH_MISO: R2312.1; also elsewhere on the board
FLASH_MOSI: R2301.2; also elsewhere on the board
FLASH_SCK: R2305.2; also elsewhere on the board
GND: C2301.2, C2302.2, C2303.2, C2304.2, R2308.2, R2310.2, R2311.2, U2301.4 (VSS), U2302.3 (GND); also elsewhere on the board
unnamed: D2301.1 (K), U2302.4
unnamed: D2301.2 (A), R2313.2
unnamed: R2301.1, R2310.1, U2301.5 (SI)
unnamed: R2302.1, R2309.2, U2301.7 (~HOLD)
unnamed: R2303.1, R2306.2, U2301.3 (~WP)
unnamed: R2304.1, R2307.2, U2301.1 (~CE)
unnamed: R2305.1, R2308.1, U2301.6 (SCK)
unnamed: R2311.1, R2312.2, U2301.2 (SO)
~FLASH_CE6: R2304.2, U2302.2; also elsewhere on the board
~FLASH_Hold: R2302.2; also elsewhere on the board
~FLASH_WP6: R2303.2; also elsewhere on the board

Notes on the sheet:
23. External FLASH 6

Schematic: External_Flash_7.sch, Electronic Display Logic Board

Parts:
C2401, C2404: 0.1uF; C_0603; Voltage 50V; Digi-Key PN 311-1344-1-ND
C2402: 10nF; C_0603; Voltage 50V; Digi-Key PN 1276-1921-1-ND
C2403: 1nF; C_0603; Voltage 50V; Digi-Key PN 1276-1018-1-ND
D2401: Green; LED_0603; Digi-Key PN 160-1446-1-ND
R2401, R2402, R2403, R2404, R2405, R2412: 100; R_0603; Tolerance 1%; Digi-Key PN A106047CT-ND
R2406, R2407, R2408, R2409, R2410, R2411: 10k; R_0603; Tolerance 1%; Digi-Key PN RMCF0603FT10K0CT-ND
R2413: 1k; R_0603; Tolerance 1%; Digi-Key PN RMCF0603FT1K00CT-ND
U2401: SST25PF020B; SOIC-8_3.9x4.9mm_Pitch1.27mm; Digi-Key PN SST25PF020B-80-4C-SAE-TCT-ND
U2402: 74LVC1G07; SOT-353_SC-70-5; Digi-Key PN 296-8486-1-ND

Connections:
+3V3: C2401.1, C2402.1, C2403.1, C2404.1, R2406.1, R2407.1, R2409.1, R2413.1, U2401.8 (VDD), U2402.5 (VCC); also elsewhere on the board
FLASH_MISO: R2412.1; also elsewhere on the board
FLASH_MOSI: R2401.2; also elsewhere on the board
FLASH_SCK: R2405.2; also elsewhere on the board
GND: C2401.2, C2402.2, C2403.2, C2404.2, R2408.2, R2410.2, R2411.2, U2401.4 (VSS), U2402.3 (GND); also elsewhere on the board
unnamed: D2401.1 (K), U2402.4
unnamed: D2401.2 (A), R2413.2
unnamed: R2401.1, R2410.1, U2401.5 (SI)
unnamed: R2402.1, R2409.2, U2401.7 (~HOLD)
unnamed: R2403.1, R2406.2, U2401.3 (~WP)
unnamed: R2404.1, R2407.2, U2401.1 (~CE)
unnamed: R2405.1, R2408.1, U2401.6 (SCK)
unnamed: R2411.1, R2412.2, U2401.2 (SO)
~FLASH_CE7: R2404.2, U2402.2; also elsewhere on the board
~FLASH_Hold: R2402.2; also elsewhere on the board
~FLASH_WP7: R2403.2; also elsewhere on the board

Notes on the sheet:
24. External FLASH 7

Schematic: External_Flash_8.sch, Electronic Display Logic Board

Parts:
C2501, C2504: 0.1uF; C_0603; Voltage 50V; Digi-Key PN 311-1344-1-ND
C2502: 10nF; C_0603; Voltage 50V; Digi-Key PN 1276-1921-1-ND
C2503: 1nF; C_0603; Voltage 50V; Digi-Key PN 1276-1018-1-ND
D2501: Green; LED_0603; Digi-Key PN 160-1446-1-ND
R2501, R2502, R2503, R2504, R2505, R2512: 100; R_0603; Tolerance 1%; Digi-Key PN A106047CT-ND
R2506, R2507, R2508, R2509, R2510, R2511: 10k; R_0603; Tolerance 1%; Digi-Key PN RMCF0603FT10K0CT-ND
R2513: 1k; R_0603; Tolerance 1%; Digi-Key PN RMCF0603FT1K00CT-ND
U2501: SST25PF020B; SOIC-8_3.9x4.9mm_Pitch1.27mm; Digi-Key PN SST25PF020B-80-4C-SAE-TCT-ND
U2502: 74LVC1G07; SOT-353_SC-70-5; Digi-Key PN 296-8486-1-ND

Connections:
+3V3: C2501.1, C2502.1, C2503.1, C2504.1, R2506.1, R2507.1, R2509.1, R2513.1, U2501.8 (VDD), U2502.5 (VCC); also elsewhere on the board
FLASH_MISO: R2512.1; also elsewhere on the board
FLASH_MOSI: R2501.2; also elsewhere on the board
FLASH_SCK: R2505.2; also elsewhere on the board
GND: C2501.2, C2502.2, C2503.2, C2504.2, R2508.2, R2510.2, R2511.2, U2501.4 (VSS), U2502.3 (GND); also elsewhere on the board
unnamed: D2501.1 (K), U2502.4
unnamed: D2501.2 (A), R2513.2
unnamed: R2501.1, R2510.1, U2501.5 (SI)
unnamed: R2502.1, R2509.2, U2501.7 (~HOLD)
unnamed: R2503.1, R2506.2, U2501.3 (~WP)
unnamed: R2504.1, R2507.2, U2501.1 (~CE)
unnamed: R2505.1, R2508.1, U2501.6 (SCK)
unnamed: R2511.1, R2512.2, U2501.2 (SO)
~FLASH_CE8: R2504.2, U2502.2; also elsewhere on the board
~FLASH_Hold: R2502.2; also elsewhere on the board
~FLASH_WP8: R2503.2; also elsewhere on the board

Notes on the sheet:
25. External FLASH 8
